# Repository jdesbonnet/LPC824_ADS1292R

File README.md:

# LPC824_ADS1292R

TI ADS1292R ECG front end IC with LPC824 microcontroller PCB. CAD software: KiCad.

Design goals:
  * Breadboard compatible breakout board format
  * Can use without LPC824 (all important pins on breakout header)
  * 3.5mm audio jack for ECG lead
  * Incorporate flash for storage
  * Coin cell
  * Option for radio (RFMxx?)

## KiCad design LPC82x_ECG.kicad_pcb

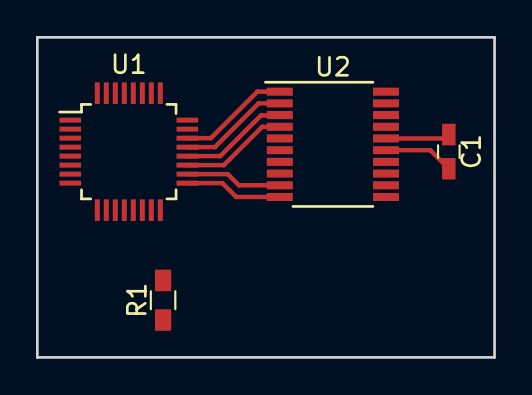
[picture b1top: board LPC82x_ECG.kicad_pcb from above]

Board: 2 copper layers, 25.4 x 17.8 mm, 4 parts (0 on the bottom side), 9 nets.

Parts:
C1: 100nF; C_0603_HandSoldering
R1: R; R_0603_HandSoldering
U1: ADS1292R; LQFP-32_5x5mm_Pitch0.5mm
U2: LPC824; TSSOP-20_4.4x6.5mm_Pitch0.65mm

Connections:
+3V3: C1.2, U2.15
GND: C1.1, R1.2, U1.24, U2.16
unnamed: R1.1, U1.14
unnamed: U1.17, U2.10
unnamed: U1.18, U2.9
unnamed: U1.19, U2.4
unnamed: U1.20, U2.3
unnamed: U1.21, U2.2
unnamed: U1.22, U2.1

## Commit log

2017-04-02 no comment
